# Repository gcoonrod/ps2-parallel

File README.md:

# PS/2 to Parallel Breakout Board

I wanted to learn about the PS/2 protocol by building a circuit to convert it from serial to parallel. I chose to use an ATTiny461A to control a PS/2 port and a 74HC164 shift register for parallel output.

## Current Design

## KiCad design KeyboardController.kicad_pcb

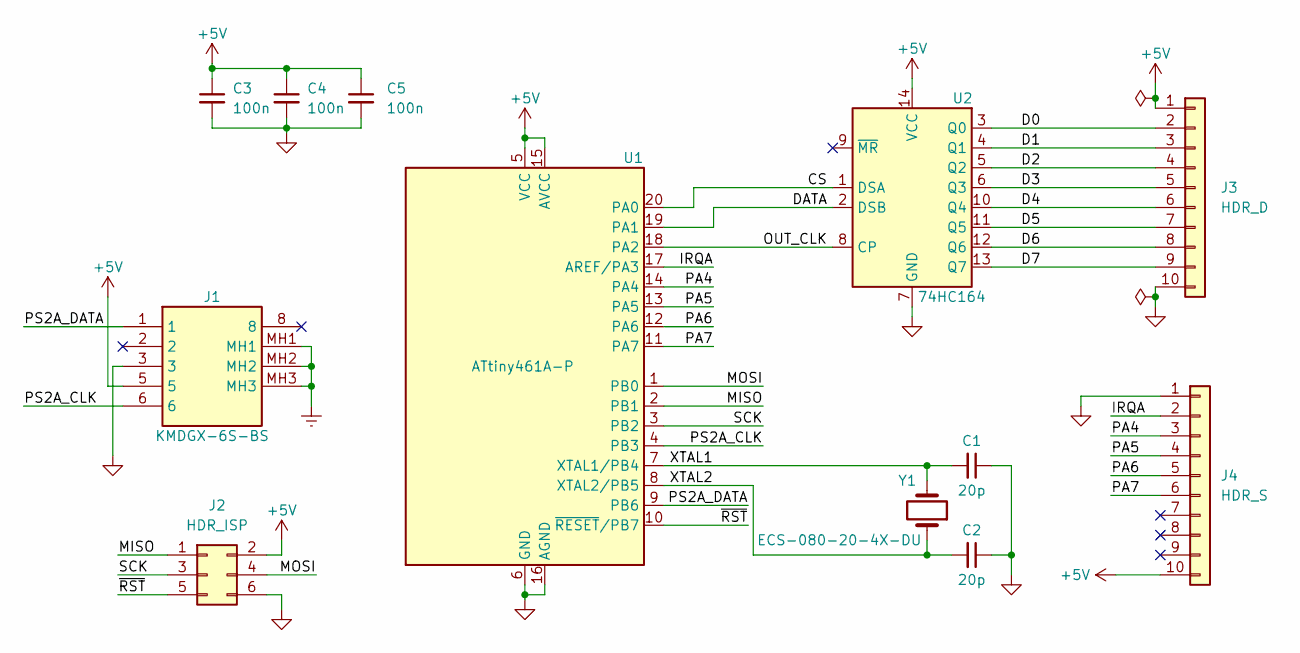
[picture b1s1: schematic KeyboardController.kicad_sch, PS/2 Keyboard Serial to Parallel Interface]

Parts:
C1, C2: 20p; C_Rect_L4.0mm_W2.5mm_P2.50mm; MFR Part C316C200F3G5TA
C3, C4, C5: 100n; C_Rect_L4.0mm_W2.5mm_P2.50mm
J1: KMDGX-6S-BS; KMDGX6SBS; Mouser Part Number 806-KMDGX-6S-BS
J2: HDR_ISP; PinHeader_2x03_P2.54mm_Vertical
J3: HDR_D; PinHeader_1x10_P2.54mm_Vertical
J4: HDR_S; PinHeader_1x10_P2.54mm_Vertical
U1: ATtiny461A-P; DIP-20_W7.62mm_Socket_LongPads
U2: 74HC164; DIP-14_W7.62mm_Socket_LongPads
Y1: ECS-080-20-4X-DU; Crystal_HC49-4H_Vertical

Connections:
+5V: C3.1, C4.1, C5.1, J1.5, J2.2, J3.1, J4.10, U1.5 (VCC), U1.15 (AVCC), U2.14 (VCC)
/CS: U1.20 (PA0), U2.1 (DSA)
/D0: J3.2, U2.3 (Q0)
/D1: J3.3, U2.4 (Q1)
/D2: J3.4, U2.5 (Q2)
/D3: J3.5, U2.6 (Q3)
/D4: J3.6, U2.10 (Q4)
/D5: J3.7, U2.11 (Q5)
/D6: J3.8, U2.12 (Q6)
/D7: J3.9, U2.13 (Q7)
/DATA: U1.19 (PA1), U2.2 (DSB)
/IRQA: J4.2, U1.17 (AREF/PA3)
/MISO: J2.1, U1.2 (PB1)
/MOSI: J2.4, U1.1 (PB0)
/OUT_CLK: U1.18 (PA2), U2.8 (CP)
/PA4: J4.3, U1.14 (PA4)
/PA5: J4.4, U1.13 (PA5)
/PA6: J4.5, U1.12 (PA6)
/PA7: J4.6, U1.11 (PA7)
/PS2A_CLK: J1.6, U1.4 (PB3)
/PS2A_DATA: J1.1, U1.9 (PB6)
/SCK: J2.3, U1.3 (PB2)
/XTAL1: C1.2, U1.7 (XTAL1/PB4), Y1.2
/XTAL2: C2.2, U1.8 (XTAL2/PB5), Y1.1
/~RST: J2.5, U1.10 (~RESET/PB7)
Earth: J1.MH1, J1.MH2, J1.MH3
GND: C1.1, C2.1, C3.2, C4.2, C5.2, J1.3, J2.6, J3.10, J4.1, U1.6 (GND), U1.16 (AGND), U2.7 (GND)

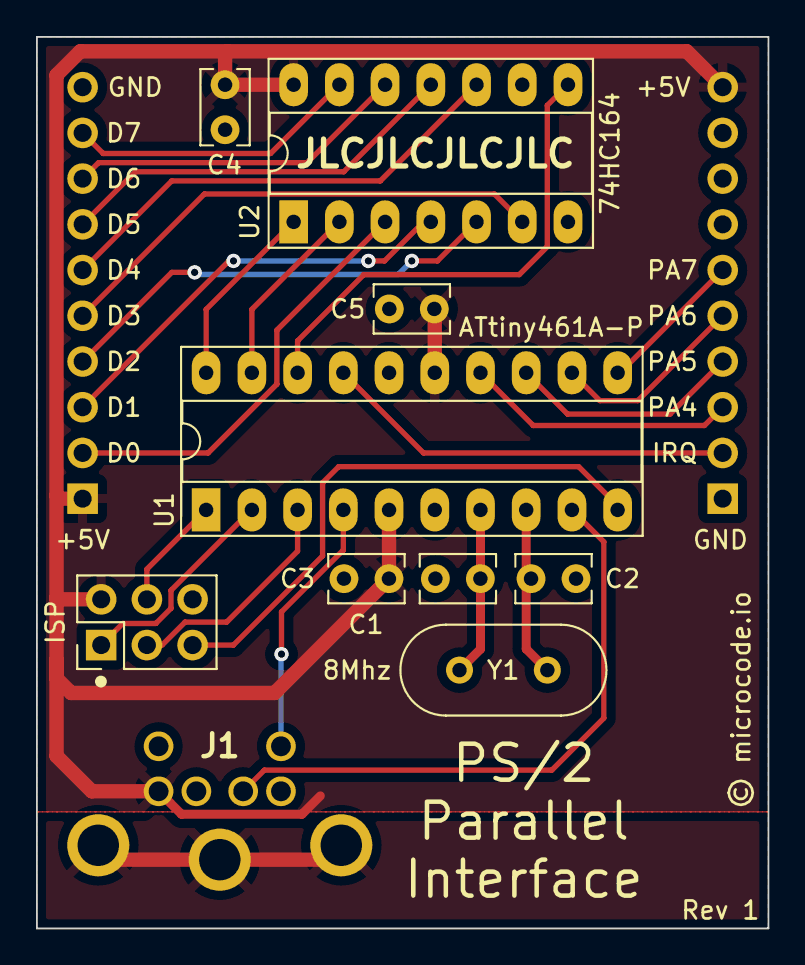
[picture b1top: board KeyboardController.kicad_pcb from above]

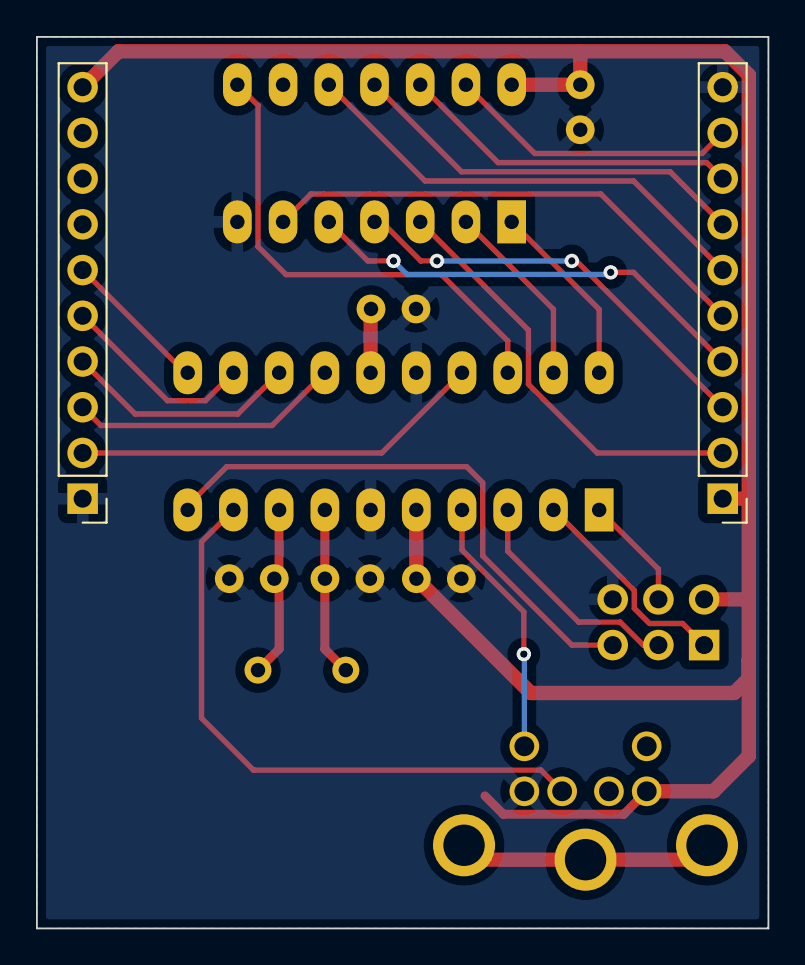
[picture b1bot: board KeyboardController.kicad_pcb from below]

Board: 2 copper layers, 40.6 x 49.5 mm, 12 parts (2 on the bottom side), 27 nets.

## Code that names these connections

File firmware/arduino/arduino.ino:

// Copyright 2023 Greg Coonrod
// 
// Licensed under the Apache License, Version 2.0 (the "License");
// you may not use this file except in compliance with the License.
// You may obtain a copy of the License at
// 
//     http://www.apache.org/licenses/LICENSE-2.0
// 
// Unless required by applicable law or agreed to in writing, software
// distributed under the License is distributed on an "AS IS" BASIS,
// WITHOUT WARRANTIES OR CONDITIONS OF ANY KIND, either express or implied.
// See the License for the specific language governing permissions and
// limitations under the License.

#include <TimerThree.h>

#define PS2_CLK 42
#define PS2_DATA 40
#define IRQA 52
#define IRQB 50
#define PA5 48
#define PA6 46
#define PA7 44

const char PDATA[] = {36, 34, 32, 30, 28, 26, 24, 22};

void setup() {
    pinMode(PS2_CLK, OUTPUT);
    pinMode(PS2_DATA, OUTPUT);

    digitalWrite(PS2_CLK, HIGH);
    digitalWrite(PS2_DATA, HIGH);

    pinMode(IRQA, INPUT);
    pinMode(IRQB, INPUT);

    for (int n = 0; n < 8; n++){
        pinMode(PDATA[n], INPUT);
    }
    
    attachInterrupt(digitalPinToInterrupt(IRQA), onIRQA, RISING);

    Timer3.initialize(5000000UL); // Every 1 seconds
    Timer3.attachInterrupt(sendScanCodeOnISR);
    
    Serial.begin(115200);
}

void ps2SendBit(uint8_t bit) {
    digitalWrite(PS2_CLK, LOW);
    delayMicroseconds(10);
    //delay(10000);
    digitalWrite(PS2_DATA, bit);
    delayMicroseconds(10);
    //delay(10000);
    digitalWrite(PS2_CLK, HIGH);
    //delay(10000);
}

void ps2SendByte(byte packet) {
    ps2SendBit(LOW);    // Start bit
    for (uint8_t i = 0; i < 8; ++i) {   // 8 data bits
        ps2SendBit(packet & 1);
        packet >>= 1;
    }
    ps2SendBit(__builtin_parity((unsigned int)packet)); // odd parity
    ps2SendBit(HIGH); // stop bit
}

void sendScanCodeOnISR() {
    //send start bit
    cli();
    ps2SendByte(0x15);
    Serial.println("Sending scan code.");
    sei();
}

void onIRQA() {
    cli();
    char output[7];
    unsigned int data = 0;
    for (int i = 0; i < 8; i++) {
        int bit = digitalRead(PDATA[i] ? 1 : 0);
        Serial.print(bit);
        data = (data << 1) + bit;
    }
    Serial.print("  ");

    sprintf(output, " %02x", data);
    Serial.print(output);
    Serial.println();
    sei();
}

void loop() {
    // Do nothing in the loop
}

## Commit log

2023-03-30 Init
2023-04-01 Board rev 1.

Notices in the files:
KeyboardController.kicad_pcb:
© microcode.io
